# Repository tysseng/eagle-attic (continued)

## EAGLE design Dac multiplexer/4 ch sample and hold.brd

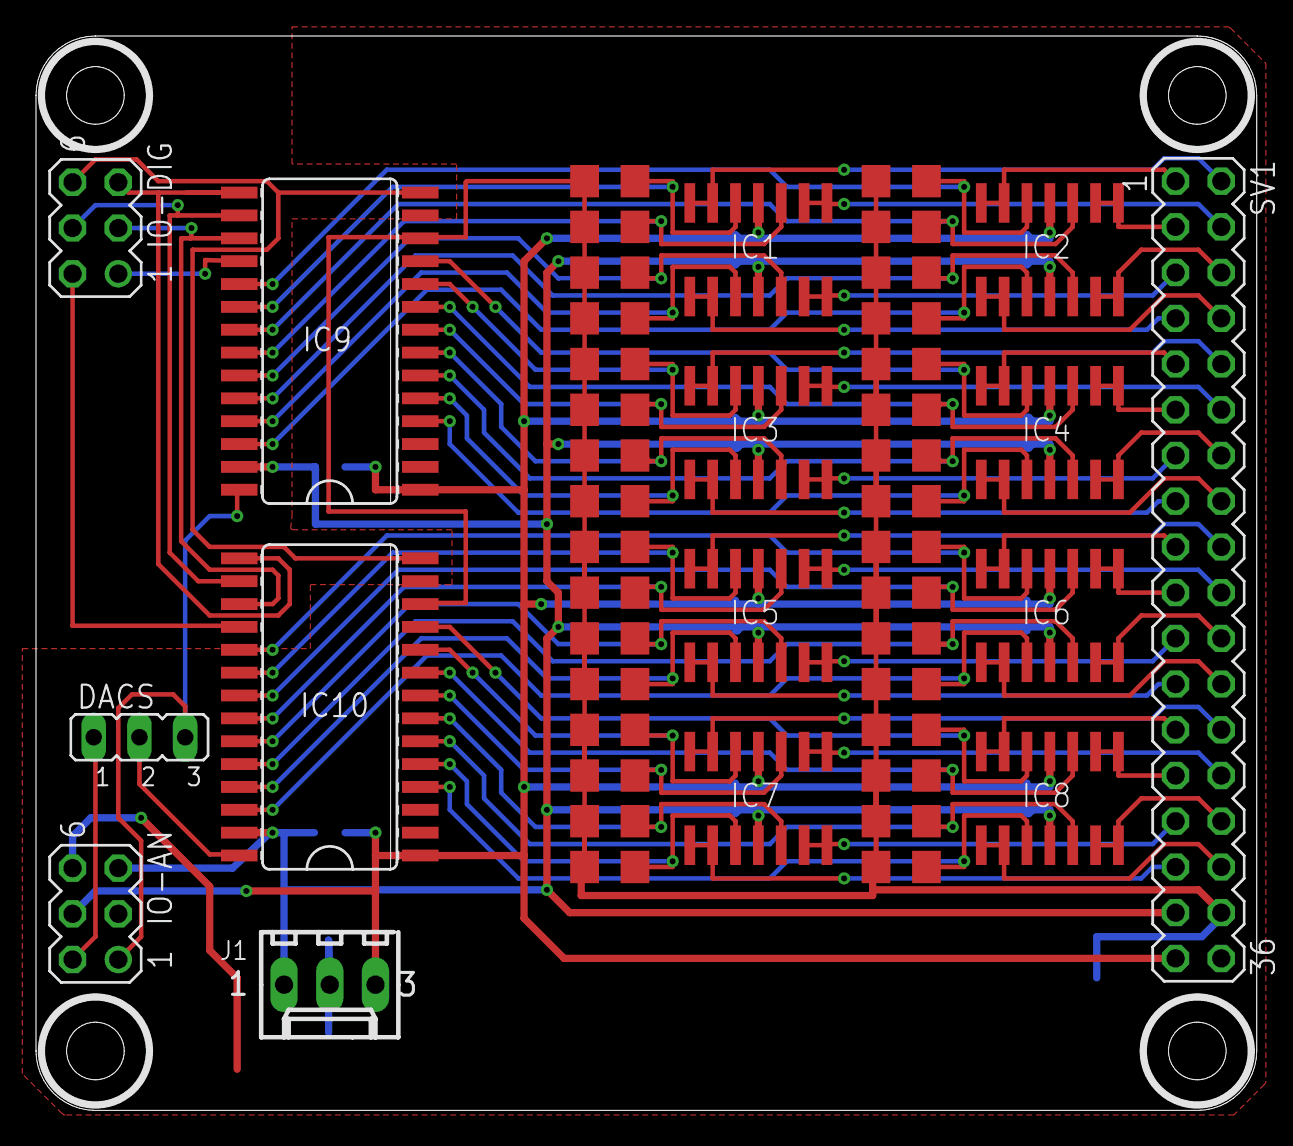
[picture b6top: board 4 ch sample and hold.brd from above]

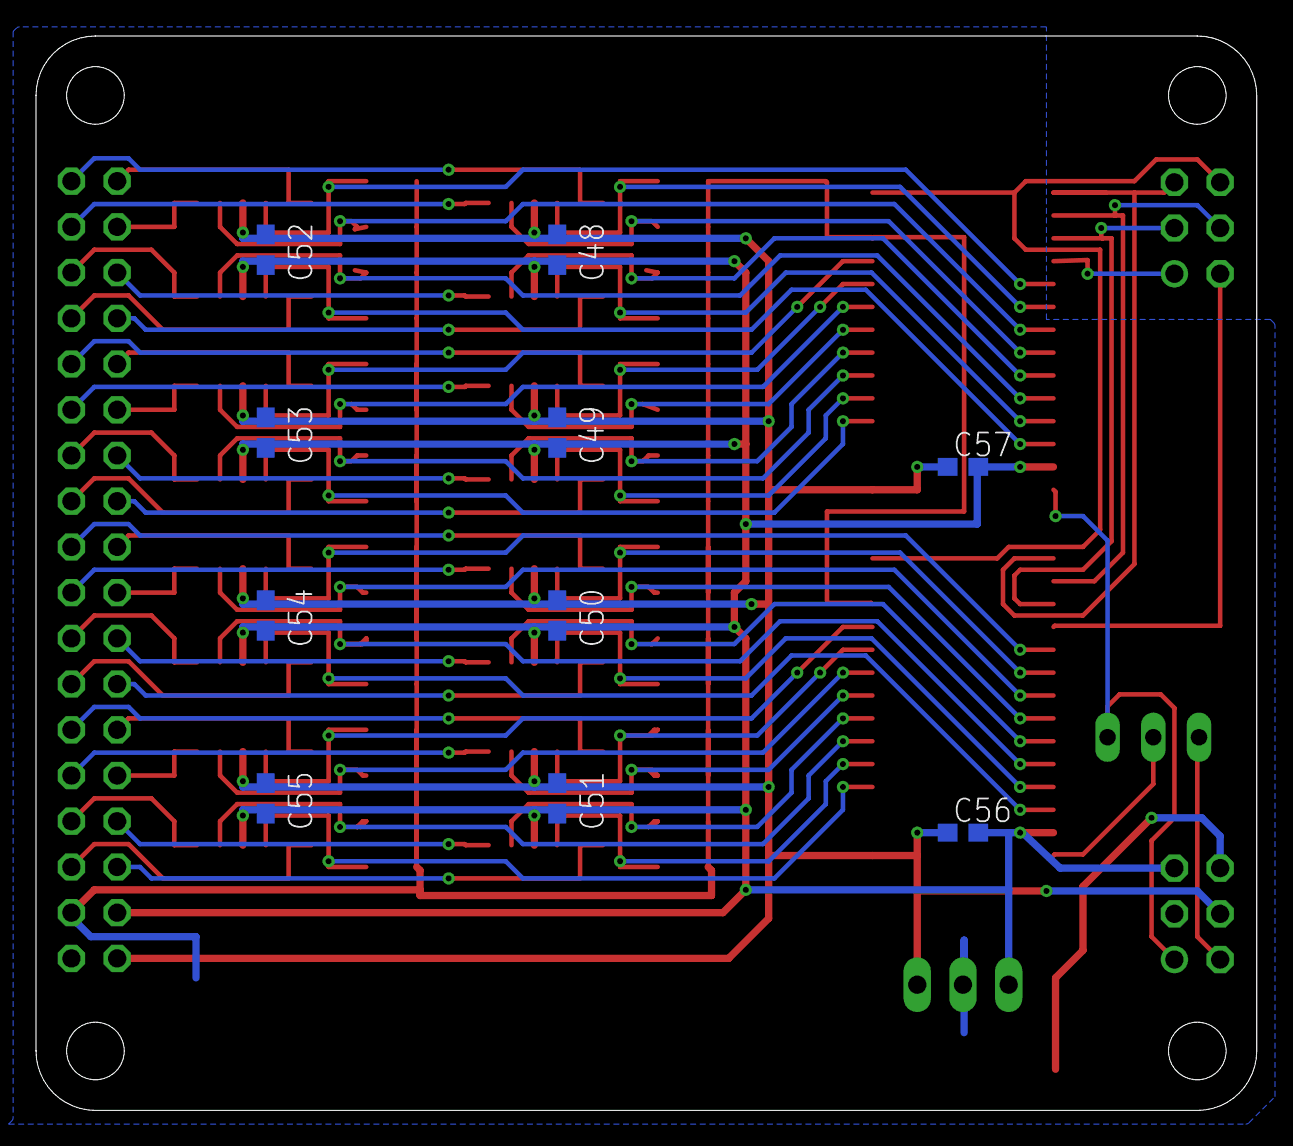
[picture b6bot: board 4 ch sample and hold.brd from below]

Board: 2 copper layers, 67.8 x 59.7 mm, 57 parts (10 on the bottom side), 76 nets.

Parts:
C1, C2, C3, C4, C5, C6, C7, C8, C9, C10, C11, C12, C13, C14, C15, C16, C17, C18, C19, C20, C21, C22, C23, C24, C25, C26, C27, C28, C29, C30, C31, C32: C1206
C48, C49, C50, C51, C52, C53, C54, C55, C56, C57: 0.1uF; C0603
DACS: JP2
IC1, IC2, IC3, IC4, IC5, IC6, IC7, IC8: TL074D; SO14
IC9, IC10: MAX306CWI; SO28L
IO-AN: MA03-2
IO-DIG: MA03-2
J1: 22-27-2031-03; 6410-03
SV1: MA18-2

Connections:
A0: IC9.17, IC10.17, IO-DIG.3
A1: IC9.16, IC10.16, IO-DIG.4
A2: IC9.15, IC10.15, IO-DIG.5
A3: IC9.14, IC10.14, IO-DIG.6
AGND: C1.1, C2.1, C3.1, C4.1, C5.1, C6.1, C7.1, C8.1, C9.1, C10.1, C11.1, C12.1, C13.1, C14.1, C15.1, C16.1, C17.1, C18.1, C19.1, C20.1, C21.1, C22.1, C23.1, C24.1, C25.1, C26.1, C27.1, C28.1, C29.1, C30.1, C31.1, C32.1, IC9.12, IC10.12, IO-AN.6, J1.2, SV1.34
EN0: IC9.18, IO-DIG.1
EN1: IC10.18, IO-DIG.2
IN0: C8.2, IC2.12, IC9.19
IN1: C4.2, IC1.12, IC9.20
IN2: C7.2, IC2.10, IC9.21
IN3: C3.2, IC1.10, IC9.22
IN4: C2.2, IC1.5, IC9.23
IN5: C6.2, IC2.5, IC9.24
IN6: C1.2, IC1.3, IC9.25
IN7: C5.2, IC2.3, IC9.26
IN8: C16.2, IC4.12, IC9.11
IN9: C12.2, IC3.12, IC9.10
IN10: C15.2, IC4.10, IC9.9
IN11: C11.2, IC3.10, IC9.8
IN12: C10.2, IC3.5, IC9.7
IN13: C14.2, IC4.5, IC9.6
IN14: C9.2, IC3.3, IC9.5
IN15: C13.2, IC4.3, IC9.4
IN16: C24.2, IC6.12, IC10.19
IN17: C20.2, IC5.12, IC10.20
IN18: C23.2, IC6.10, IC10.21
IN19: C19.2, IC5.10, IC10.22
IN20: C18.2, IC5.5, IC10.23
IN21: C22.2, IC6.5, IC10.24
IN22: C17.2, IC5.3, IC10.25
IN23: C21.2, IC6.3, IC10.26
IN24: C32.2, IC8.12, IC10.11
IN25: C28.2, IC7.12, IC10.10
IN26: C31.2, IC8.10, IC10.9
IN27: C27.2, IC7.10, IC10.8
IN28: C26.2, IC7.5, IC10.7
IN29: C30.2, IC8.5, IC10.6
IN30: C25.2, IC7.3, IC10.5
IN31: C29.2, IC8.3, IC10.4
OUT0: IC2.13, IC2.14, SV1.1
OUT1: IC1.13, IC1.14, SV1.2
OUT2: IC2.8, IC2.9, SV1.3
OUT3: IC1.8, IC1.9, SV1.4
OUT4: IC1.6, IC1.7, SV1.5
OUT5: IC2.6, IC2.7, SV1.6
OUT6: IC1.1, IC1.2, SV1.7
OUT7: IC2.1, IC2.2, SV1.8
OUT8: IC4.13, IC4.14, SV1.9
OUT9: IC3.13, IC3.14, SV1.10
OUT10: IC4.8, IC4.9, SV1.11
OUT11: IC3.8, IC3.9, SV1.12
OUT12: IC3.6, IC3.7, SV1.13
OUT13: IC4.6, IC4.7, SV1.14
OUT14: IC3.1, IC3.2, SV1.15
OUT15: IC4.1, IC4.2, SV1.16
OUT16: IC6.13, IC6.14, SV1.17
OUT17: IC5.13, IC5.14, SV1.18
OUT18: IC6.8, IC6.9, SV1.19
OUT19: IC5.8, IC5.9, SV1.20
OUT20: IC5.6, IC5.7, SV1.21
OUT21: IC6.6, IC6.7, SV1.22
OUT22: IC5.1, IC5.2, SV1.23
OUT23: IC6.1, IC6.2, SV1.24
OUT24: IC8.13, IC8.14, SV1.25
OUT25: IC7.13, IC7.14, SV1.26
OUT26: IC8.8, IC8.9, SV1.27
OUT27: IC7.8, IC7.9, SV1.28
OUT28: IC7.6, IC7.7, SV1.29
OUT29: IC8.6, IC8.7, SV1.30
OUT30: IC7.1, IC7.2, SV1.31
OUT31: IC8.1, IC8.2, SV1.32
V+: C48.2, C49.2, C50.2, C51.2, C52.2, C53.2, C54.2, C55.2, C56.2, C57.2, IC1.4, IC2.4, IC3.4, IC4.4, IC5.4, IC6.4, IC7.4, IC8.4, IC9.27, IC10.27, IO-AN.5, J1.1, SV1.33
V-: C48.1, C49.1, C50.1, C51.1, C52.1, C53.1, C54.1, C55.1, C56.1, C57.1, IC1.11, IC2.11, IC3.11, IC4.11, IC5.11, IC6.11, IC7.11, IC8.11, IC9.1, IC10.1, IO-AN.4, J1.3, SV1.35
VOUT1: DACS.3, IC9.28, IO-AN.1
VOUT2: DACS.1, IO-AN.2
VOUT-JMP: DACS.2, IC10.28

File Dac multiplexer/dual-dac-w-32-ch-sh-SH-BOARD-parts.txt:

Partlist

Exported from dual-dac-w-32-ch-sh-SH-BOARD.sch at 01.03.2015 13:32:01

EAGLE Version 7.2.0 Copyright (c) 1988-2014 CadSoft

Assembly variant: 

Part     Value          Device        Package  Library   Sheet

C1                      C-EUC1206     C1206    resistor  1
C2                      C-EUC1206     C1206    resistor  1
C3                      C-EUC1206     C1206    resistor  1
C4                      C-EUC1206     C1206    resistor  1
C5                      C-EUC1206     C1206    resistor  1
C6                      C-EUC1206     C1206    resistor  1
C7                      C-EUC1206     C1206    resistor  1
C8                      C-EUC1206     C1206    resistor  1
C9                      C-EUC1206     C1206    resistor  1
C10                     C-EUC1206     C1206    resistor  1
C11                     C-EUC1206     C1206    resistor  1
C12                     C-EUC1206     C1206    resistor  1
C13                     C-EUC1206     C1206    resistor  1
C14                     C-EUC1206     C1206    resistor  1
C15                     C-EUC1206     C1206    resistor  1
C16                     C-EUC1206     C1206    resistor  1
C17                     C-EUC1206     C1206    resistor  1
C18                     C-EUC1206     C1206    resistor  1
C19                     C-EUC1206     C1206    resistor  1
C20                     C-EUC1206     C1206    resistor  1
C21                     C-EUC1206     C1206    resistor  1
C22                     C-EUC1206     C1206    resistor  1
C23                     C-EUC1206     C1206    resistor  1
C24                     C-EUC1206     C1206    resistor  1
C25                     C-EUC1206     C1206    resistor  1
C26                     C-EUC1206     C1206    resistor  1
C27                     C-EUC1206     C1206    resistor  1
C28                     C-EUC1206     C1206    resistor  1
C29                     C-EUC1206     C1206    resistor  1
C30                     C-EUC1206     C1206    resistor  1
C31                     C-EUC1206     C1206    resistor  1
C32                     C-EUC1206     C1206    resistor  1

C48      0.1uF          C-EUC0603     C0603    resistor  1
C49      0.1uF          C-EUC0603     C0603    resistor  1
C50      0.1uF          C-EUC0603     C0603    resistor  1
C51      0.1uF          C-EUC0603     C0603    resistor  1
C52      0.1uF          C-EUC0603     C0603    resistor  1
C53      0.1uF          C-EUC0603     C0603    resistor  1
C54      0.1uF          C-EUC0603     C0603    resistor  1
C55      0.1uF          C-EUC0603     C0603    resistor  1
C56      0.1uF          C-EUC0603     C0603    resistor  1
C57      0.1uF          C-EUC0603     C0603    resistor  1

DACS                    JP2E          JP2      jumper    1
IC1      TL074D         TL074D        SO14     linear    1
IC2      TL074D         TL074D        SO14     linear    1
IC3      TL074D         TL074D        SO14     linear    1
IC4      TL074D         TL074D        SO14     linear    1
IC5      TL074D         TL074D        SO14     linear    1
IC6      TL074D         TL074D        SO14     linear    1
IC7      TL074D         TL074D        SO14     linear    1
IC8      TL074D         TL074D        SO14     linear    1

IC9      MAX306CWI      MAX306CWI     SO28L    maxim     1
IC10     MAX306CWI      MAX306CWI     SO28L    maxim     1
IO-AN                   MA03-2        MA03-2   con-lstb  1
IO-DIG                  MA03-2        MA03-2   con-lstb  1
J1       22-27-2031-03  22-27-2031-03 6410-03  con-molex 1
SV1                     MA18-2        MA18-2   con-lstb  1
